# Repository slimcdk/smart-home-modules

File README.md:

# Hardware components for home automation

## Saved for furter reading
https://github.com/xesscorp/kicad-3rd-party-tools

## Setup
To fetch submodules, run the command:
```
$ git submodule update --init
```

## Contribute
You are very welcome to do pull requests. Before doing so, please read the repository guidelines.

### Repository structure

KiCad can not handle libaries outside its project folders. Therefore common libraries must be places in ```include/libs/kicad``` and any project then symlinks this directory.

E.g. this will create a symbolic link ```libs```inside the kicad project.
```
$ cd mains-light-controller/circuits
$ ln -s ./../../include/libs/kicad ./libs
```

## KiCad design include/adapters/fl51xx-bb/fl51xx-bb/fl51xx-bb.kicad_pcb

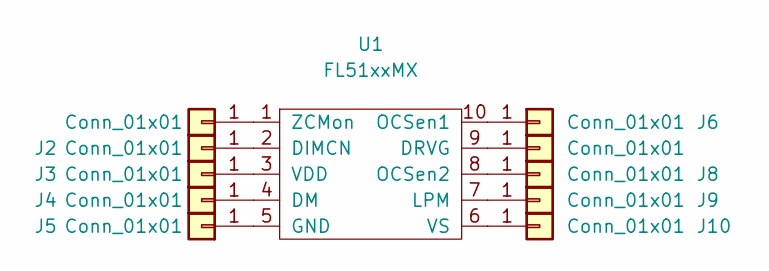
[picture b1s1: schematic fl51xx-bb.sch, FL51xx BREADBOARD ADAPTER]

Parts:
J1, J2, J3, J4, J5, J6, J7, J8, J9, J10: Conn_01x01; PinHeader_1x01_P2.54mm_Vertical
U1: FL51xxMX

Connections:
unnamed: J1.1, U1.1 (ZCMon)
unnamed: J2.1, U1.2 (DIMCN)
unnamed: J3.1, U1.3 (VDD)
unnamed: J4.1, U1.4 (DM)
unnamed: J5.1, U1.5 (GND)
unnamed: J6.1, U1.10 (OCSen1)
unnamed: J7.1, U1.9 (DRVG)
unnamed: J8.1, U1.8 (OCSen2)
unnamed: J9.1, U1.7 (LPM)
unnamed: J10.1, U1.6 (VS)

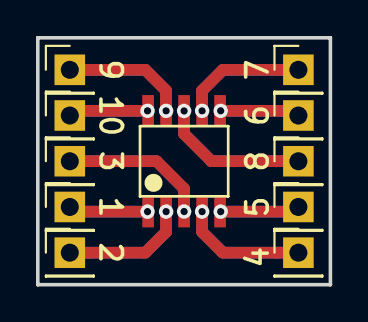
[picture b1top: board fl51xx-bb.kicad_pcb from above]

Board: 2 copper layers, 16.3 x 13.7 mm, 11 parts (0 on the bottom side), 10 nets.

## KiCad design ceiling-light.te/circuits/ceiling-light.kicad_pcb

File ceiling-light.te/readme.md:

<h1>Ceiling Light Controller</h1>

This component can control any loads of mains voltage (120-240VAC) up to 5A.
Requires constant power and sensing line (main switch) to function as intended.

<hr>
<h3>Power inputs</h3>
<ul>
    <li>M1: Power from switches</li>
    <li>M2: Constant power supply</li>
    <li>N: Neutral</li>
</ul>

<hr>
<h2>Circuit Design</h2>
<p>Schematic</p>

<p>PCB layout</p>

<div style="height: 500px; width:100%">
  
  <div style="float:left; height: 100%; width:auto;">
    <ul>
      <li><a href="exports/ceiling-light-Edge.Cuts.svg">Edge Cuts</a></li>
      <li><a href="exports/ceiling-light-F.SilkS.svg">Silkscreen Top</a></li>
      <li><a href="exports/ceiling-light-B.SilkS.svg">Silkscreen Bottom</a></li>  
      <li><a href="exports/ceiling-light-F.Mask.svg">Soldermask Top</a></li>
      <li><a href="exports/ceiling-light-B.Mask.svg">Soldermask Bottom</a></li>
      <li><a href="exports/ceiling-light-F.Cu.svg">Copper Top</a></li>
      <li><a href="exports/ceiling-light-B.Cu.svg">Copper Bottom</a></li>
    </ul>
  </div>

  <div style="margin-left:auto; margin-right:auto; height:100%; width:100%;">

  </div>
</div>

<!--hr>

<h2> BOM (Bill of Materials) </h2>
<table style="text-align:left">
  <tr><th>#</th>  <th>Quantity</th> <th>Part</th>                     <th>Section</th>        <th>Link</th>  </tr>
  <tr><td>1</td>  <td>1</td>        <td>WeMos D1 (ESP8266)</td>       <td>Controller</td>     <td></td>      </tr>
  <tr><td>2</td>  <td>1</td>        <td>WS1228b RGB LED</td>          <td></td>               <td></td>      </tr>
  <tr><td>3</td>  <td>1</td>        <td>LDR</td>                      <td></td>               <td></td>      </tr>
  <tr><td>4</td>  <td>1</td>        <td>1/4W 10k Ohms resistor</td>   <td></td>               <td></td>      </tr>
  <tr><td>5</td>  <td>1</td>        <td>01x02 Screw terminal 
                                          (5.08mm pin spacing)</td>   <td></td>               <td></td>      </tr>
  <tr><td>6</td>  <td>1</td>        <td>01x03 Screw terminal 
                                          (5.08mm pin spacing)</td>   <td></td>               <td></td>      </tr>
  <tr><td>7</td>  <td>1</td>        <td>DB107 Full bridge 
                                          rectifier</td>              <td>Sensing</td>        <td></td>      </tr>
  <tr><td>8</td>  <td>1</td>        <td>LTV-817 Optocoupler</td>      <td></td>               <td></td>      </tr>
  <tr><td>9</td>  <td>1</td>        <td>1µf Electrolytic capacitor 
                                          (min 50V)</td>              <td></td>               <td></td>      </tr>
  <tr><td>10</td> <td>1</td>        <td>1/2W 10k Ohms resistor</td>   <td></td>               <td></td>      </tr>
  <tr><td>11</td> <td>1</td>        <td>HLK-PM05 AC-DC 5V voltage 
                                          regulator</td>              <td></td>               <td></td>      </tr>
  <tr><td>12</td> <td>1</td>        <td>MOC3021 Optocoupler</td>      <td>Load switcher</td>  <td></td>      </tr>
  <tr><td>13</td> <td>1</td>        <td>BT136 Triac (500V)</td>       <td></td>               <td></td>      </tr>
  <tr><td>14</td> <td>1</td>        <td>1/2W 100 Ohms resistor</td>   <td></td>               <td></td>      </tr>
  <tr><td>15</td> <td>1</td>        <td>1/2W 10k Ohms resistor</td>   <td></td>               <td></td>      </tr>
  <tr><td>16</td> <td>1</td>        <td>1/2W 330 Ohms resistor</td>   <td></td>               <td></td>      </tr>
  <tr><td>17</td> <td>1</td>        <td>1/2W 100nf Ceramic 
                                          capacitor</td>              <td></td>               <td></td>      </tr>
</table-->

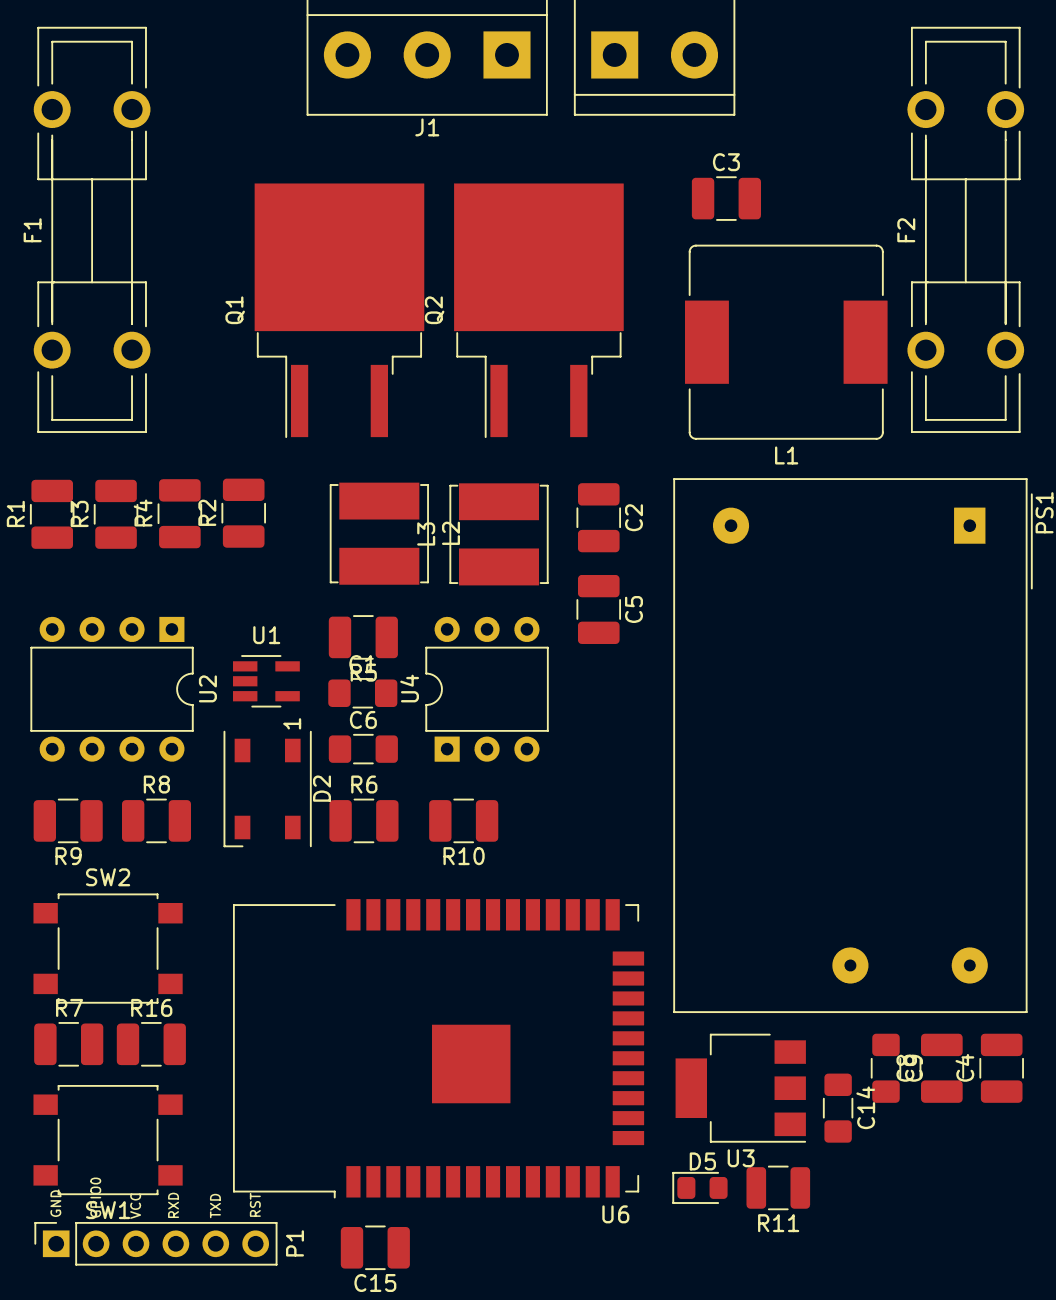
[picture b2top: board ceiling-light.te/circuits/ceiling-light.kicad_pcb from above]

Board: 2 copper layers, 42 parts (0 on the bottom side), 29 nets, no tracks yet.

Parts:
C1, C6: 0.1µ; C_1206_3216Metric_Pad1.42x1.75mm_HandSolder
C2, C3, C5, C8: 100n; C_1210_3225Metric_Pad1.42x2.65mm_HandSolder
C4: 10µF; C_1210_3225Metric_Pad1.42x2.65mm_HandSolder
C9: 47µ; C_1206_3216Metric_Pad1.42x1.75mm_HandSolder
C14: 22µF; C_1206_3216Metric_Pad1.42x1.75mm_HandSolder
C15: 10µ; C_1210_3225Metric_Pad1.42x2.65mm_HandSolder
D2: WS2812B; LED_WS2812B_PLCC4_5.0x5.0mm_P3.2mm
D5: LED; LED_0805_2012Metric_Pad1.15x1.40mm_HandSolder
F1, F2: Fuse; Fuseholder5x20_horiz_open_lateral_Type-II
J1: Screw_Terminal_01x03; TerminalBlock_bornier-3_P5.08mm
J2: Screw_Terminal_01x02; TerminalBlock_bornier-2_P5.08mm
L1: 100µH; L_Bourns_SRR1210A
L2, L3: 100µH; L_Bourns_SRN6045TA
P1: ESProg_Mating_Header; ESProg_PinSocket_1x06_P2.54mm_Vertical
PS1: IRM-02-12; Converter_ACDC_MeanWell_IRM-02-xx_THT
Q1, Q2: IRF840; TO-263-2_TabPin1
R1, R2, R3, R4: 100K; R_1210_3225Metric_Pad1.42x2.65mm_HandSolder
R5, R7, R8, R9, R16: 10K; R_1210_3225Metric_Pad1.42x2.65mm_HandSolder
R6: 1K; R_1210_3225Metric_Pad1.42x2.65mm_HandSolder
R10: 330; R_1210_3225Metric_Pad1.42x2.65mm_HandSolder
R11: 400R; R_1210_3225Metric
SW1, SW2: SW_Push; SW_SPST_B3S-1000
U1: TMP36xS; SOT-23-5_HandSoldering
U2: LTV-824; DIP-8_W7.62mm
U3: AMS1117-3.3; SOT-223
U4: 4N35; DIP-6_W7.62mm
U6: ESP32-WROOM-32D; ESP32-WROOM-32

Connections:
+3V3: C6.1, C14.1, C15.1, D2.1, P1.3, R7.1, R8.1, R9.1, R11.1, R16.1, U3.2, U6.2
+12V: C4.2, C8.2, C9.1, PS1.4, U3.3, U4.5
/ESP32_BOOT: P1.2, R7.2, SW2.2, U6.25
/ESP32_RST: P1.6, R16.2, SW1.2, U6.3
/ESP32_RXD: P1.4, U6.34
/ESP32_TXD: P1.5, U6.35
GND: C1.2, C4.1, C6.2, C8.1, C9.2, C14.2, C15.2, D2.3, D5.1, P1.1, PS1.3, R5.2, R6.2, SW1.1, SW2.1, U1.4, U2.5, U2.7, U3.1, U4.2, U6.1, U6.15, U6.38
unnamed: C1.1, U1.5
unnamed: C2.1, F1.1, L2.1, Q1.2, R1.2, R3.2
unnamed: C2.2, C3.1, J1.1, J2.1, L3.2
unnamed: C3.2, F2.1, L1.1
unnamed: C5.1, L3.1, PS1.1
unnamed: C5.2, L2.2, PS1.2
unnamed: D2.4, R6.1, U6.7
unnamed: D5.2, R11.2
unnamed: F1.2, J1.3
unnamed: F2.2, J2.2
unnamed: J1.2, R2.2, R4.2
unnamed: L1.2, Q2.2
unnamed: Q1.1, Q2.1, R5.1, U4.4
unnamed: R1.1, U2.3
unnamed: R2.1, U2.4
unnamed: R3.1, U2.1
unnamed: R4.1, U2.2
unnamed: R8.2, U2.8, U6.14
unnamed: R9.2, U2.6, U6.13
unnamed: R10.1, U6.37
unnamed: R10.2, U4.1
unnamed: U1.1, U6.4

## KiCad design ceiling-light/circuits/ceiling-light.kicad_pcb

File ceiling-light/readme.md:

<h1>Ceiling Light Controller</h1>

This component can control any loads of mains voltage (120-240VAC) up to 5A.
Requires constant power and sensing line (main switch) to function as intended.

<hr>
<h3>Power inputs</h3>
<ul>
    <li>M1: Power from switches</li>
    <li>M2: Constant power supply</li>
    <li>N: Neutral</li>
</ul>

<hr>
<h2>Circuit Design</h2>
<p>Schematic</p>

<p>PCB layout</p>

<div style="height: 500px; width:100%">
  
  <div style="float:left; height: 100%; width:auto;">
    <ul>
      <li><a href="exports/ceiling-light-Edge.Cuts.svg">Edge Cuts</a></li>
      <li><a href="exports/ceiling-light-F.SilkS.svg">Silkscreen Top</a></li>
      <li><a href="exports/ceiling-light-B.SilkS.svg">Silkscreen Bottom</a></li>  
      <li><a href="exports/ceiling-light-F.Mask.svg">Soldermask Top</a></li>
      <li><a href="exports/ceiling-light-B.Mask.svg">Soldermask Bottom</a></li>
      <li><a href="exports/ceiling-light-F.Cu.svg">Copper Top</a></li>
      <li><a href="exports/ceiling-light-B.Cu.svg">Copper Bottom</a></li>
    </ul>
  </div>

  <div style="margin-left:auto; margin-right:auto; height:100%; width:100%;">

  </div>
</div>

<hr>

<h2> BOM (Bill of Materials) </h2>
<table style="text-align:left">
  <tr><th>#</th>  <th>Quantity</th> <th>Part</th>                     <th>Section</th>        <th>Link</th>  </tr>
  <tr><td>1</td>  <td>1</td>        <td>WeMos D1 (ESP8266)</td>       <td>Controller</td>     <td></td>      </tr>
  <tr><td>2</td>  <td>1</td>        <td>WS1228b RGB LED</td>          <td></td>               <td></td>      </tr>
  <tr><td>3</td>  <td>1</td>        <td>LDR</td>                      <td></td>               <td></td>      </tr>
  <tr><td>4</td>  <td>1</td>        <td>1/4W 10k Ohms resistor</td>   <td></td>               <td></td>      </tr>
  <tr><td>5</td>  <td>1</td>        <td>01x02 Screw terminal 
                                          (5.08mm pin spacing)</td>   <td></td>               <td></td>      </tr>
  <tr><td>6</td>  <td>1</td>        <td>01x03 Screw terminal 
                                          (5.08mm pin spacing)</td>   <td></td>               <td></td>      </tr>
  <tr><td>7</td>  <td>1</td>        <td>DB107 Full bridge 
                                          rectifier</td>              <td>Sensing</td>        <td></td>      </tr>
  <tr><td>8</td>  <td>1</td>        <td>LTV-817 Optocoupler</td>      <td></td>               <td></td>      </tr>
  <tr><td>9</td>  <td>1</td>        <td>1µf Electrolytic capacitor 
                                          (min 50V)</td>              <td></td>               <td></td>      </tr>
  <tr><td>10</td> <td>1</td>        <td>1/2W 10k Ohms resistor</td>   <td></td>               <td></td>      </tr>
  <tr><td>11</td> <td>1</td>        <td>HLK-PM05 AC-DC 5V voltage 
                                          regulator</td>              <td></td>               <td></td>      </tr>
  <tr><td>12</td> <td>1</td>        <td>MOC3021 Optocoupler</td>      <td>Load switcher</td>  <td></td>      </tr>
  <tr><td>13</td> <td>1</td>        <td>BT136 Triac (500V)</td>       <td></td>               <td></td>      </tr>
  <tr><td>14</td> <td>1</td>        <td>1/2W 100 Ohms resistor</td>   <td></td>               <td></td>      </tr>
  <tr><td>15</td> <td>1</td>        <td>1/2W 10k Ohms resistor</td>   <td></td>               <td></td>      </tr>
  <tr><td>16</td> <td>1</td>        <td>1/2W 330 Ohms resistor</td>   <td></td>               <td></td>      </tr>
  <tr><td>17</td> <td>1</td>        <td>1/2W 100nf Ceramic 
                                          capacitor</td>              <td></td>               <td></td>      </tr>
</table>

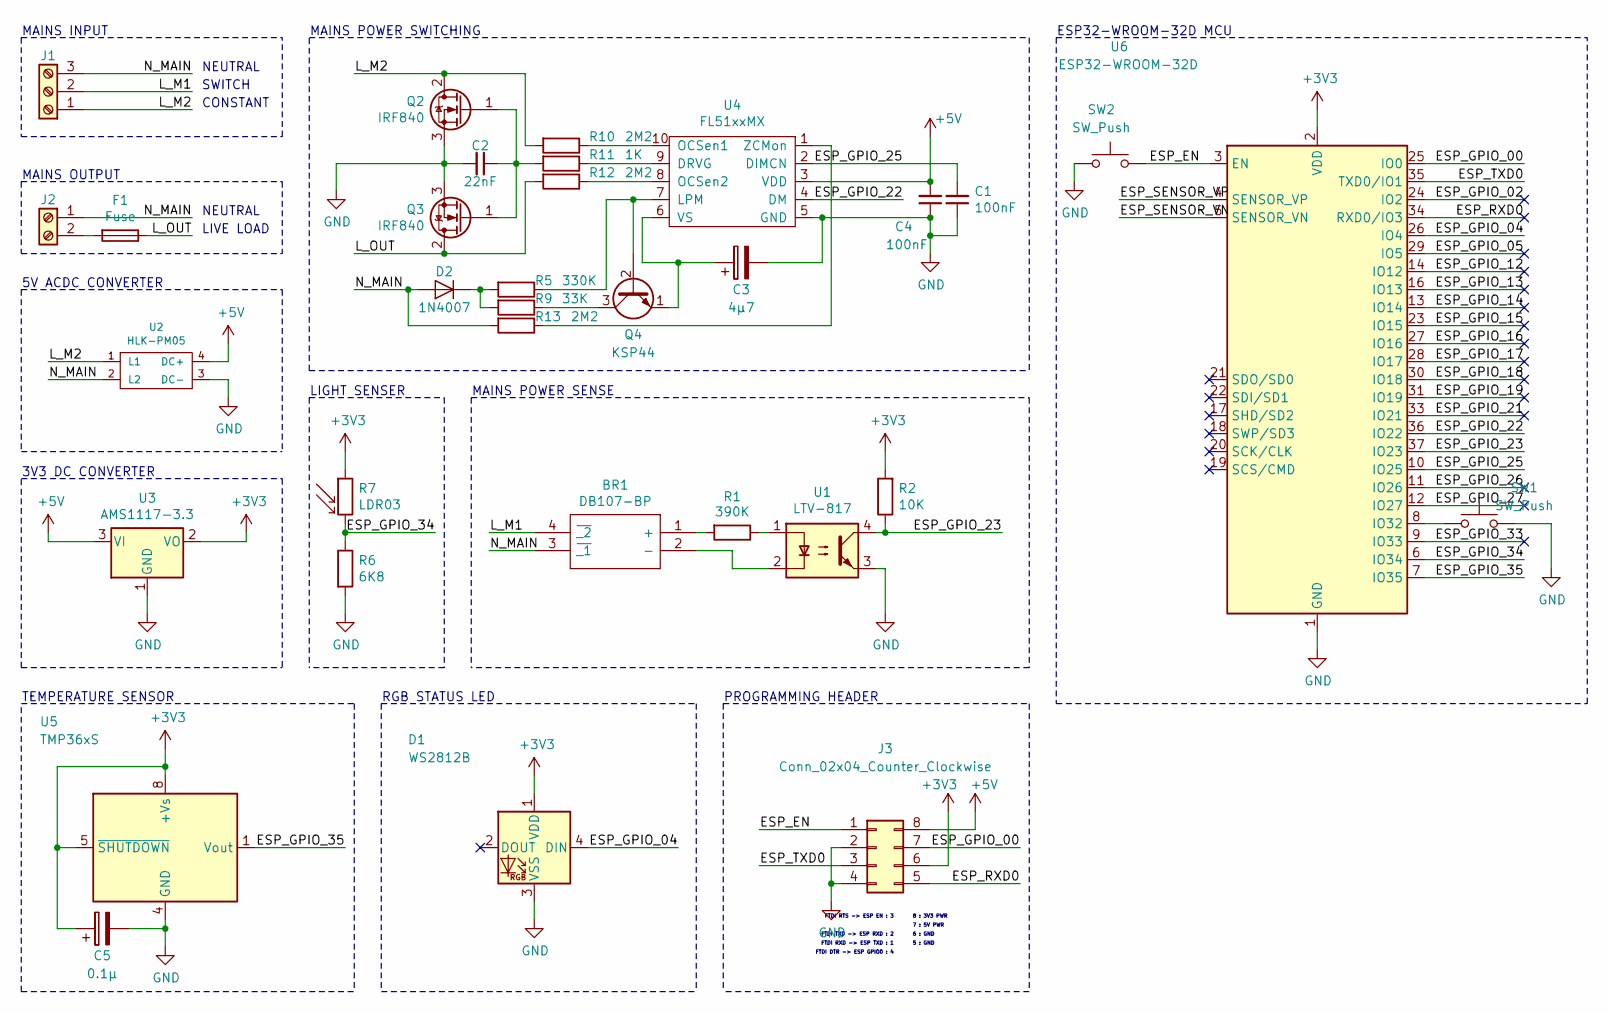
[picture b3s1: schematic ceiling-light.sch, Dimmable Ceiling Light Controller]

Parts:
BR1: DB107-BP; Manufacturer_Part_Number DB107-BP; Mouser Part Number 833-DB107-BP
C1, C4: 100nF; CP_Radial_D5.0mm_P2.50mm
C2: 22nF; CP_Radial_D5.0mm_P2.50mm
C3: 4µ7; CP_Radial_D5.0mm_P2.50mm
C5: 0.1µ; CP_Radial_D5.0mm_P2.50mm
D1: WS2812B; LED_WS2812B_PLCC4_5.0x5.0mm_P3.2mm
D2: 1N4007; D_DO-41_SOD81_P10.16mm_Horizontal
F1: Fuse; Fuseholder5x20_horiz_open_lateral_Type-II
J1: Screw_Terminal_01x03; TerminalBlock_bornier-3_P5.08mm
J2: Screw_Terminal_01x02; TerminalBlock_bornier-2_P5.08mm
J3: Conn_02x04_Counter_Clockwise; PinSocket_2x04_P2.54mm_Vertical
Q2, Q3: IRF840; TO-263-3_TabPin2
Q4: KSP44; TO-92_Inline
R1: 390K; R_Axial_DIN0207_L6.3mm_D2.5mm_P10.16mm_Horizontal
R2: 10K; R_Axial_DIN0207_L6.3mm_D2.5mm_P10.16mm_Horizontal
R5: 330K; R_Axial_DIN0207_L6.3mm_D2.5mm_P10.16mm_Horizontal
R6: 6K8; R_Axial_DIN0207_L6.3mm_D2.5mm_P10.16mm_Horizontal
R7: LDR03; R_LDR_5.0x4.1mm_P3mm_Vertical
R9: 33K; R_Axial_DIN0207_L6.3mm_D2.5mm_P10.16mm_Horizontal
R10, R12, R13: 2M2; R_Axial_DIN0411_L9.9mm_D3.6mm_P12.70mm_Horizontal
R11: 1K; R_Axial_DIN0207_L6.3mm_D2.5mm_P10.16mm_Horizontal
SW1, SW2: SW_Push; SW_Tactile_Straight_KSA0Axx1LFTR
U1: LTV-817; DIP-4_W7.62mm
U2: HLK-PM05; HLK-PM01
U3: AMS1117-3.3; SOT-223-3_TabPin2
U4: FL51xxMX
U5: TMP36xS; SOIC-8_3.9x4.9mm_P1.27mm
U6: ESP32-WROOM-32D; ESP32-WROOM-32

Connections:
+3V3: C5.1, D1.1 (VDD), J3.6, R2.2, R7.1, U3.2 (VO), U5.5 (~SHUTDOWN), U5.8 (+Vs), U6.2 (VDD)
+5V: C4.2, J3.8, U2.4 (DC+), U3.3 (VI), U4.3 (VDD)
/ESP_EN: J3.1, SW2.2, U6.3 (EN)
/ESP_GPIO_00: J3.7, U6.25 (IO0)
/ESP_GPIO_02: U6.24 (IO2)
/ESP_GPIO_04: D1.4 (DIN), U6.26 (IO4)
/ESP_GPIO_05: U6.29 (IO5)
/ESP_GPIO_12: U6.14 (IO12)
/ESP_GPIO_13: U6.16 (IO13)
/ESP_GPIO_14: U6.13 (IO14)
/ESP_GPIO_15: U6.23 (IO15)
/ESP_GPIO_16: U6.27 (IO16)
/ESP_GPIO_17: U6.28 (IO17)
/ESP_GPIO_18: U6.30 (IO18)
/ESP_GPIO_19: U6.31 (IO19)
/ESP_GPIO_21: U6.33 (IO21)
/ESP_GPIO_22: U4.4 (DM), U6.36 (IO22)
/ESP_GPIO_23: R2.1, U1.4, U6.37 (IO23)
/ESP_GPIO_25: C1.2, U4.2 (DIMCN), U6.10 (IO25)
/ESP_GPIO_26: U6.11 (IO26)
/ESP_GPIO_27: U6.12 (IO27)
/ESP_GPIO_33: U6.9 (IO33)
/ESP_GPIO_34: R6.1, R7.2, U6.6 (IO34)
/ESP_GPIO_35: U5.1 (Vout), U6.7 (IO35)
/ESP_RXD0: J3.5, U6.34 (RXD0/IO3)
/ESP_SENSOR_VN: U6.5 (SENSOR_VN)
/ESP_SENSOR_VP: U6.4 (SENSOR_VP)
/ESP_TXD0: J3.3, U6.35 (TXD0/IO1)
/L_M1: BR1.4 (~_2), J1.2
/L_M2: J1.1, Q2.2 (D), R10.2, U2.1 (L1)
/L_OUT: F1.1, Q3.2 (D), R12.2
/N_MAIN: BR1.3 (~_1), D2.2 (A), J1.3, J2.1, R13.2, U2.2 (L2)
GND: C1.1, C2.2, C3.2, C4.1, C5.2, D1.3 (VSS), J3.2, J3.4, Q2.3 (S), Q3.3 (S), R6.2, SW1.2, SW2.1, U1.3, U2.3 (DC-), U3.1 (GND), U4.5 (GND), U5.4 (GND), U6.1 (GND), U6.15 (GND), U6.38 (GND)
unnamed: BR1.1 (+), R1.2
unnamed: BR1.2 (-), U1.2
unnamed: C2.1, Q2.1 (G), Q3.1 (G), R11.2
unnamed: C3.1, Q4.1 (E), U4.6 (VS)
unnamed: D2.1 (K), R5.2, R9.2
unnamed: F1.2, J2.2
unnamed: Q4.2 (B), R5.1, U4.7 (LPM)
unnamed: Q4.3 (C), R9.1
unnamed: R1.1, U1.1
unnamed: R10.1, U4.10 (OCSen1)
unnamed: R11.1, U4.9 (DRVG)
unnamed: R12.1, U4.8 (OCSen2)
unnamed: R13.1, U4.1 (ZCMon)
unnamed: SW1.1, U6.8 (IO32)

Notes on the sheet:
NEUTRAL
SWITCH
CONSTANT
LIVE LOAD
MAINS INPUT
5V ACDC CONVERTER
MAINS POWER SENSE
MAINS POWER SWITCHING
MAINS OUTPUT
LIGHT SENSER
RGB STATUS LED
3V3 DC CONVERTER
TEMPERATURE SENSOR
ESP32-WROOM-32D MCU
8 : 3V3 PWR
FTDI RTS -> ESP EN : 3
FTDI TXD -> ESP RXD : 2
FTDI RXD -> ESP TXD : 1
5 : GND
7 : 5V PWR
PROGRAMMING HEADER
6 : GND
FTDI DTR -> ESP GPIO0 : 4

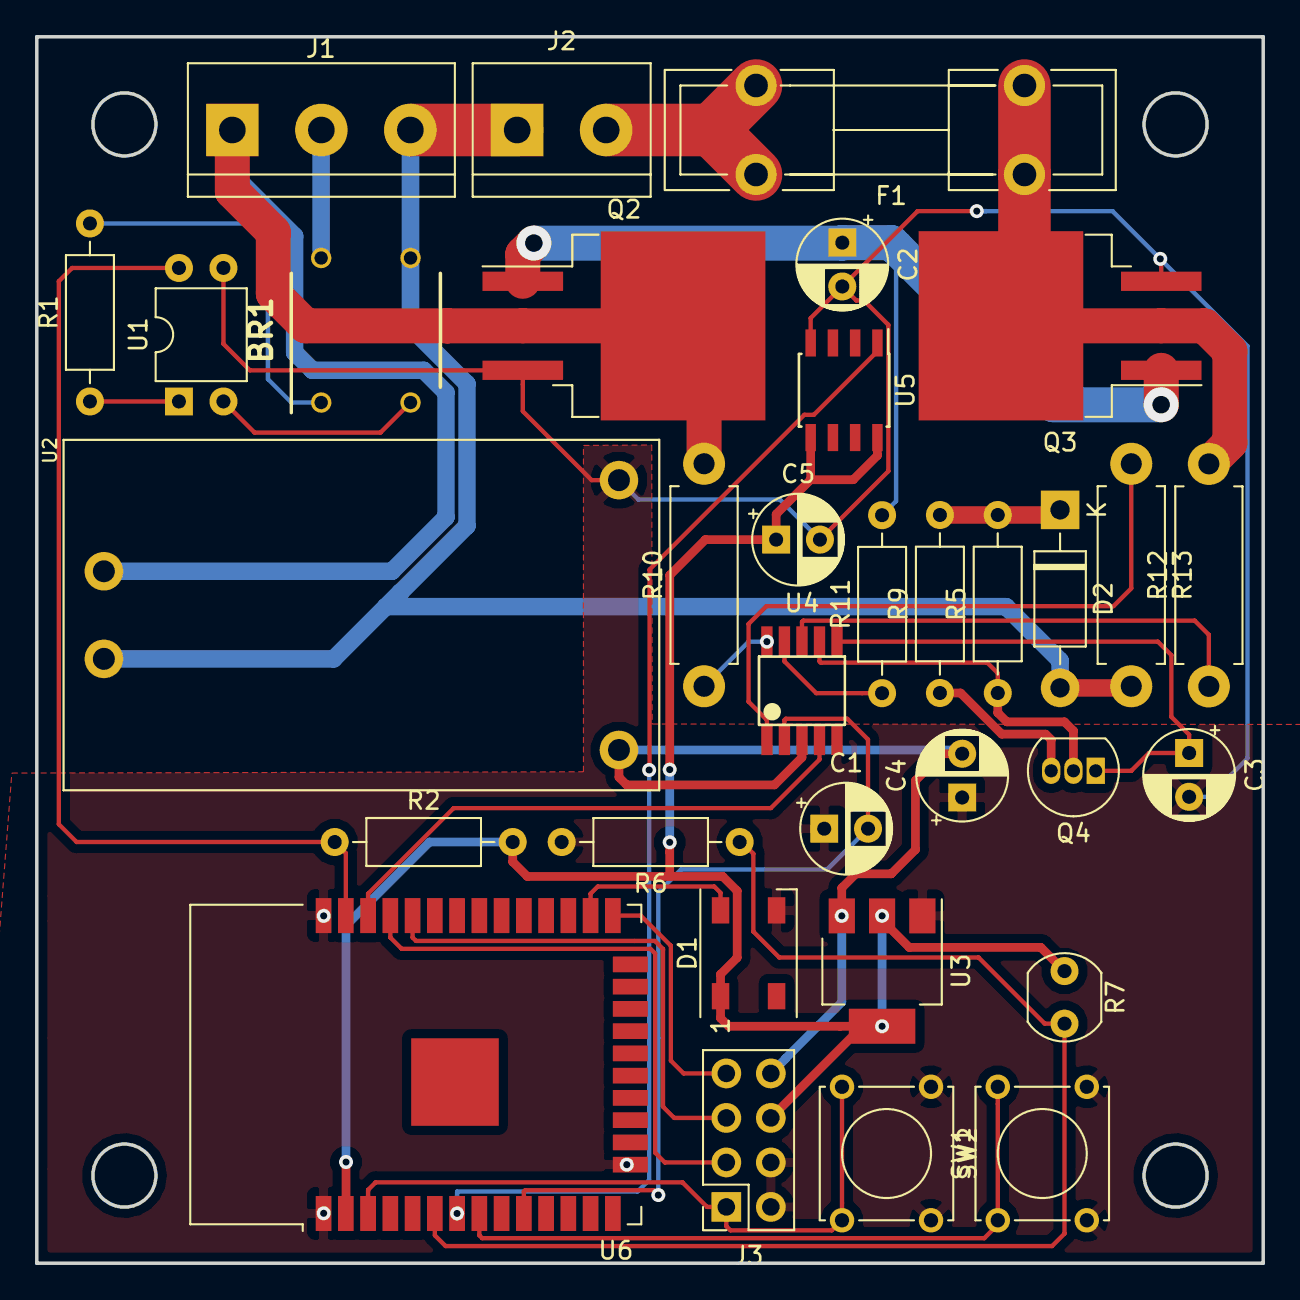
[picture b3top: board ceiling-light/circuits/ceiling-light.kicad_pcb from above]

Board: 2 copper layers, 70.0 x 70.0 mm, 33 parts (0 on the bottom side), 31 nets.

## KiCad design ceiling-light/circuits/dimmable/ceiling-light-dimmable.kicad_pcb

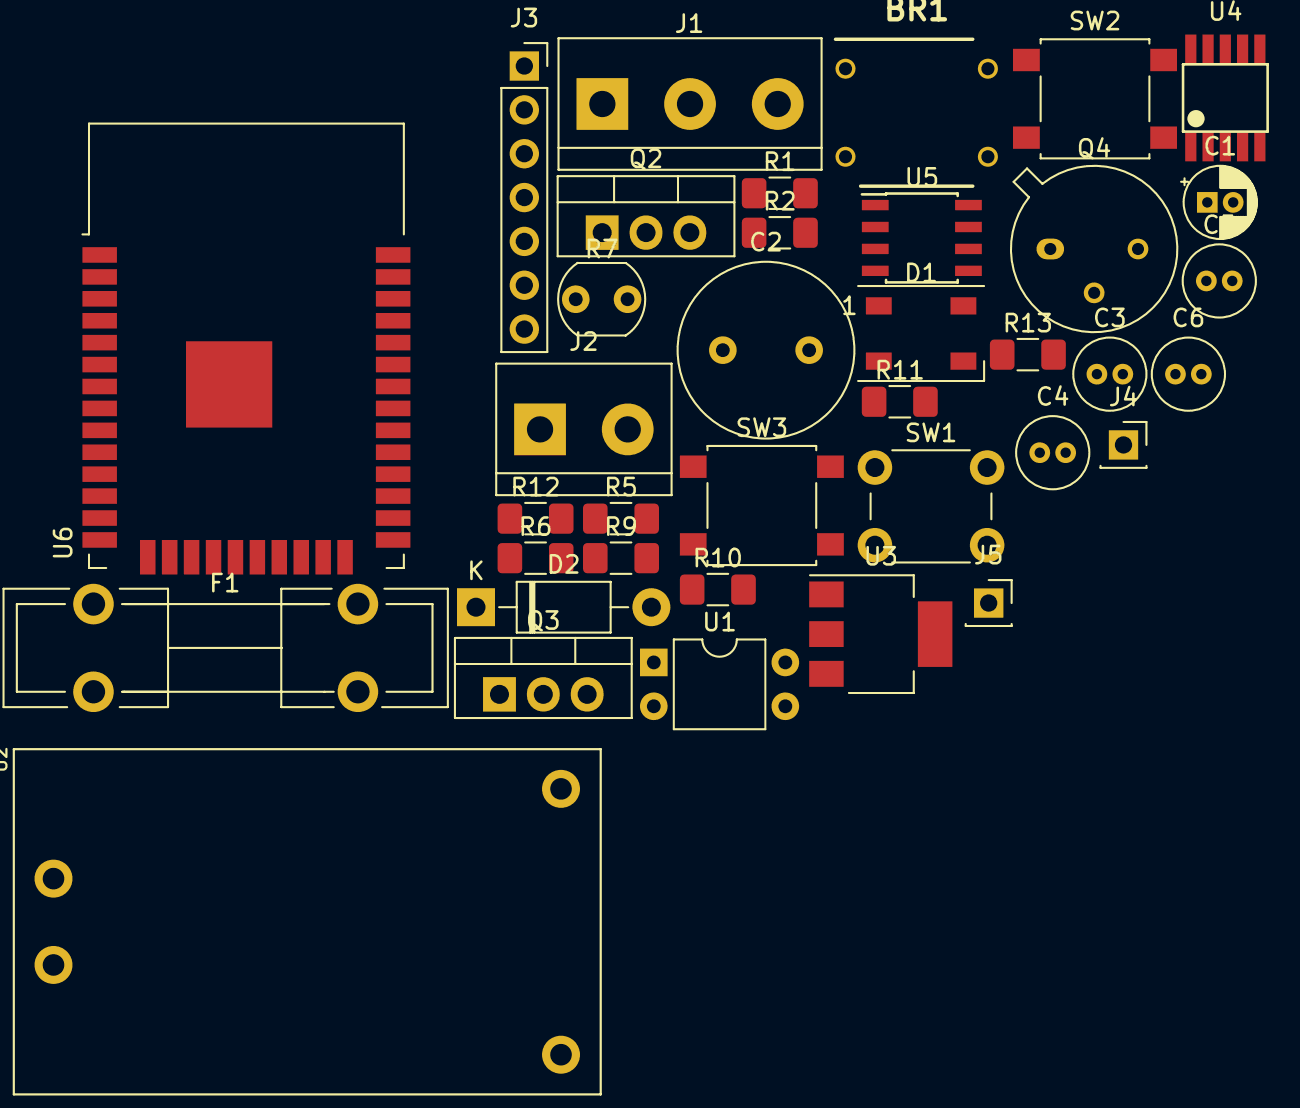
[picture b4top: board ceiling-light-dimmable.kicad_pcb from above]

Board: 2 copper layers, 37 parts (0 on the bottom side), 31 nets, no tracks yet.

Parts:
BR1: DB107-BP
C1: 1µF; CP_Radial_D4.0mm_P1.50mm
C2: 22nF; C_Radial_D10.0mm_H12.5mm_P5.00mm
C3: 22nF; C_Radial_D4.0mm_H5.0mm_P1.50mm
C4: 100nF; C_Radial_D4.0mm_H5.0mm_P1.50mm
C5, C6: 0.1µF; C_Radial_D4.0mm_H5.0mm_P1.50mm
D1: WS2812B; LED_WS2812B_PLCC4_5.0x5.0mm_P3.2mm
D2: 1N4007; D_DO-41_SOD81_P10.16mm_Horizontal
F1: Fuse; Fuseholder5x20_horiz_open_lateral_Type-II
J1: Screw_Terminal_01x03; TerminalBlock_bornier-3_P5.08mm
J2: Screw_Terminal_01x02; TerminalBlock_bornier-2_P5.08mm
J3: Conn_01x07; PinSocket_1x07_P2.54mm_Vertical
J4, J5: Conn_01x01; PinSocket_1x01_P2.54mm_Vertical
Q2, Q3: IRF840; TO-220-3_Vertical
Q4: KSP44; TO-39-3
R1: 390K; R_1206_3216Metric_Pad1.42x1.75mm_HandSolder
R2: 10K; R_1206_3216Metric_Pad1.42x1.75mm_HandSolder
R5: 330K; R_1206_3216Metric_Pad1.42x1.75mm_HandSolder
R6: 6K8; R_1206_3216Metric_Pad1.42x1.75mm_HandSolder
R7: LDR03; R_LDR_5.0x4.1mm_P3mm_Vertical
R9: 33K; R_1206_3216Metric_Pad1.42x1.75mm_HandSolder
R10, R12, R13: 2M; R_1206_3216Metric_Pad1.42x1.75mm_HandSolder
R11: 1K; R_1206_3216Metric_Pad1.42x1.75mm_HandSolder
SW1: SW_Push; SW_PUSH_6mm
SW2, SW3: SW_Push; SW_SPST_B3S-1000
U1: LTV-817; DIP-4_W7.62mm
U2: HLK-PM05; HLK-PM01
U3: AMS1117-3.3; SOT-223-3_TabPin2
U4: FL51xxMX
U5: TMP36xS; SOIC-8_3.9x4.9mm_P1.27mm
U6: ESP32-WROOM-32D; ESP32-WROOM-32

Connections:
+3V3: C5.1, C6.1, D1.1, J3.6, R2.2, R7.1, U3.2, U5.5, U5.8, U6.2
+5V: C4.2, J3.1, U2.4, U3.3, U4.8
/DIMCN: J4.1, U4.9
/DIM_MODE: J5.1, U4.7
/ESP_FLASH: J3.5, SW3.1, U6.25
/ESP_RX: J3.4, U6.34
/ESP_TX: J3.3, U6.35
/LIGHT_SENSE: R6.1, R7.2, U6.5
/L_OUT: F1.1, Q3.2, R12.2
/M1_IN: BR1.4, J1.2
/M2_IN: J1.1, Q2.2, R10.2, U2.1
/MAINS_SENSE: C1.1, R2.1, U1.4, U6.6
/N_MAIN: BR1.3, D2.2, J1.3, J2.1, R13.1, U2.2
/STATUS_LED: D1.4, U6.9
/TEMP_SENSE: U5.1, U6.4
GND: C1.2, C2.2, C3.2, C4.1, C5.2, C6.2, D1.3, J3.2, J3.7, Q2.3, Q3.3, R6.2, SW1.2, SW2.1, SW3.2, U1.3, U2.3, U3.1, U4.6, U5.4, U6.1, U6.15, U6.38
unnamed: BR1.1, R1.2
unnamed: BR1.2, U1.2
unnamed: C2.1, Q2.1, Q3.1, R11.2
unnamed: C3.1, Q4.1, U4.5
unnamed: D2.1, R5.2, R9.2
unnamed: F1.2, J2.2
unnamed: Q4.2, R5.1, U4.4
unnamed: Q4.3, R9.1
unnamed: R1.1, U1.1
unnamed: R10.1, U4.1
unnamed: R11.1, U4.2
unnamed: R12.1, U4.3
unnamed: R13.2, U4.10
unnamed: SW1.1, U6.8
unnamed: SW2.2, U6.3

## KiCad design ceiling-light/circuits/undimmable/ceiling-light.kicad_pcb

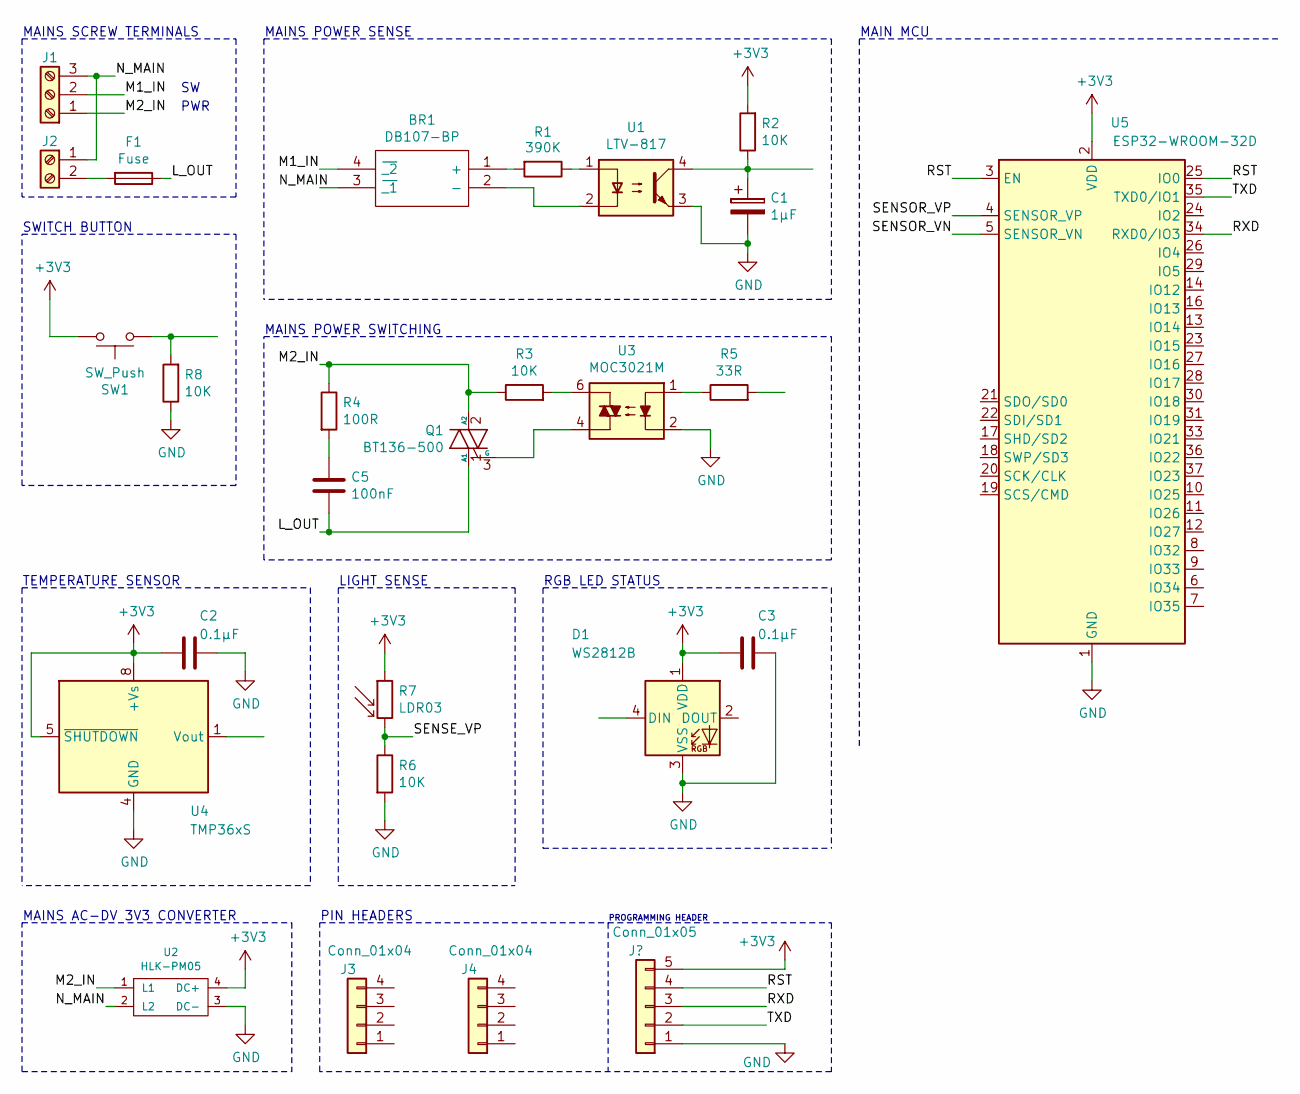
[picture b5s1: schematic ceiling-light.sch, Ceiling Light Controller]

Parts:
BR1: DB107-BP; DIP825W56P510L828H330Q4N; Manufacturer_Part_Number DB107-BP; Mouser Part Number 833-DB107-BP
C1: 1µF; CP_Radial_D4.0mm_P1.50mm
C2, C3: 0.1µF; C_Disc_D5.1mm_W3.2mm_P5.00mm
C5: 100nF; C_Disc_D5.1mm_W3.2mm_P5.00mm
D1: WS2812B; LED_WS2812B_PLCC4_5.0x5.0mm_P3.2mm
F1: Fuse; Fuseholder5x20_horiz_open_lateral_Type-II
J1: Screw_Terminal_01x03; TerminalBlock_bornier-3_P5.08mm
J2: Screw_Terminal_01x02; TerminalBlock_bornier-2_P5.08mm
J3, J4: Conn_01x04; PinHeader_1x04_P2.54mm_Vertical
Q1: BT136-500; TO-220-3_Horizontal_TabUp
R1: 390K; R_1206_3216Metric_Pad1.42x1.75mm_HandSolder
R2, R3, R6, R8: 10K; R_1206_3216Metric_Pad1.42x1.75mm_HandSolder
R4: 100R; R_2010_5025Metric_Pad1.52x2.65mm_HandSolder
R5: 33R; R_1206_3216Metric_Pad1.42x1.75mm_HandSolder
R7: LDR03; R_LDR_5.0x4.1mm_P3mm_Vertical
SW1: SW_Push; SW_PUSH_6mm
U1: LTV-817; DIP-4_W7.62mm
U2: HLK-PM05; HLK-PM01
U3: MOC3021M; DIP-6_W7.62mm
U4: TMP36xS; SOIC-8_3.9x4.9mm_P1.27mm
U5: ESP32-WROOM-32D; ESP32-WROOM-32

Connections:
+3V3: C2.2, C3.2, D1.1 (VDD), R2.2, R7.1, SW1.2, U2.4 (DC+), U4.5 (~SHUTDOWN), U4.8 (+Vs), U5.2 (VDD)
/RXD: U5.34 (RXD0/IO3); also elsewhere on the board
/TXD: U5.35 (TXD0/IO1); also elsewhere on the board
GND: C1.2, C2.1, C3.1, D1.3 (VSS), R6.2, R8.1, U1.3, U2.3 (DC-), U3.2, U4.4 (GND), U5.1 (GND), U5.15 (GND), U5.38 (GND); also elsewhere on the board
L_OUT: C5.2, F1.1, Q1.1 (A1)
M1_IN: BR1.4 (~_2), J1.2
M2_IN: J1.1, Q1.2 (A2), R3.1, R4.1, U2.1 (L1)
N_MAIN: BR1.3 (~_1), J1.3, J2.1, U2.2 (L2)
unnamed: BR1.1 (+), R1.2
unnamed: BR1.2 (-), U1.2
unnamed: C1.1, R2.1, U1.4
unnamed: C5.1, R4.2
unnamed: F1.2, J2.2
unnamed: Q1.3 (G), U3.4
unnamed: R1.1, U1.1
unnamed: R3.2, U3.6
unnamed: R5.1, U3.1
unnamed: R6.1, R7.2
unnamed: R8.2, SW1.1

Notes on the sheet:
PWR
MAINS SCREW TERMINALS
MAINS AC-DV 3V3 CONVERTER
MAINS POWER SENSE
MAINS POWER SWITCHING
LIGHT SENSE
RGB LED STATUS
SWITCH BUTTON
TEMPERATURE SENSOR
MAIN MCU
PIN HEADERS
PROGRAMMING HEADER

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
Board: 2 copper layers, 27 parts (0 on the bottom side), 19 nets, no tracks yet.

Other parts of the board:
J5: Conn_01x04; PinHeader_1x04_P2.54mm_Vertical

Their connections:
/RXD: J5.3; also elsewhere on the board
/TXD: J5.4; also elsewhere on the board
GND: J5.1; also elsewhere on the board

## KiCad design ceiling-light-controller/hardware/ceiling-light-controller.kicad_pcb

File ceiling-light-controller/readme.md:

# Ceiling Light Controller

This component fits the general ceiling light socket in Denmark.

<hr>
<h3>Inputs</h3>
<ul>
    <li>M1: Power from switches</li>
    <li>M2: Constant power supply</li>
    <li>N: Neutral</li>
</ul>

<br>
<hr>

<h3> Parts list </h3>
<table style="text-align:left">
  <tr> <th>#</th> <th>Quantity</th>  <th>Part</th> <th>Section</th> <th>Link</th> </tr>
  <tr> <td>1</td> <td>1</td> <td>WeMos D1 (ESP8266)</td> <td>Controller</td> <td></td> </tr>
  <tr> <td>2</td> <td>1</td> <td>WS1228b RGB LED</td> <td></td> <td></td> </tr>
  <tr> <td>3</td> <td>1</td> <td>LDR</td> <td></td> <td></td> </tr>
  <tr> <td>4</td> <td>1</td> <td>1/4W 10k Ohms resistor</td> <td></td> <td></td> </tr>
  <tr> <td>5</td> <td>1</td> <td>01x02 Screw terminal (5.08mm pin spacing)</td> <td></td> <td></td> </tr>
  <tr> <td>6</td> <td>1</td> <td>01x03 Screw terminal (5.08mm pin spacing)</td> <td></td> <td></td> </tr>
  <tr> <td>7</td> <td>1</td> <td>DB107 Full bridge rectifier</td> <td>Sensing</td> <td></td> </tr>
  <tr> <td>8</td> <td>1</td> <td>LTV-817 Optocoupler</td> <td></td> <td></td> </tr>
  <tr> <td>9</td> <td>1</td> <td>1µf Electrolytic capacitor (min 50V)</td> <td></td> <td></td> </tr>
  <tr> <td>10</td> <td>1</td> <td>1/2W 10k Ohms resistor</td> <td></td> <td></td> </tr>
  <tr> <td>11</td> <td>1</td> <td>HLK-PM05 AC-DC 5V voltage regulator</td> <td></td> <td></td> </tr>
  <tr> <td>12</td> <td>1</td> <td>MOC3021 Optocoupler</td> <td>Load controller</td> <td></td> </tr>
  <tr> <td>13</td> <td>1</td> <td>BT136 Triac (500V)</td> <td></td> <td></td> </tr>
  <tr> <td>14</td> <td>1</td> <td>1/2W 100 Ohms resistor</td> <td></td> <td></td> </tr>
  <tr> <td>15</td> <td>1</td> <td>1/2W 10k Ohms resistor</td> <td></td> <td></td> </tr>
  <tr> <td>16</td> <td>1</td> <td>1/2W 330 Ohms resistor</td> <td></td> <td></td> </tr>
  <tr> <td>17</td> <td>1</td> <td>1/2W 100nf Ceramic capacitor</td> <td></td> <td></td> </tr>
</table>

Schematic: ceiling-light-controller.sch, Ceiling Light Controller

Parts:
BR1: DB107-BP; DIP825W56P510L828H330Q4N; Manufacturer_Part_Number DB107-BP; Mouser Part Number 833-DB107-BP
C1: 1µf; CP_Radial_D4.0mm_P1.50mm
C5: 100nf; C_Disc_D5.1mm_W3.2mm_P5.00mm
D1: WS2812B; LED_WS2812B_PLCC4_5.0x5.0mm_P3.2mm
J1: Screw_Terminal_01x03; TerminalBlock_bornier-3_P5.08mm
J2: Screw_Terminal_01x02; TerminalBlock_bornier-2_P5.08mm
Q1: BT136-500; TO-220-3_Vertical_Triode_Heatsink
R1: 390k; R_Axial_DIN0309_L9.0mm_D3.2mm_P12.70mm_Horizontal
R2, R3: 10k; R_Axial_DIN0309_L9.0mm_D3.2mm_P12.70mm_Horizontal
R4: 100; R_Axial_DIN0309_L9.0mm_D3.2mm_P12.70mm_Horizontal
R5: 330; R_Axial_DIN0309_L9.0mm_D3.2mm_P12.70mm_Horizontal
R6: 10000; R_Axial_DIN0309_L9.0mm_D3.2mm_P12.70mm_Horizontal
R7: LDR03; R_LDR_10x8.5mm_P7.6mm_Vertical
U1: LTV-817; DIP-4_W7.62mm
U2: HLK-PM03; HLK-PM01
U3: MOC3021M; DIP-6_W7.62mm
U4: WeMos_mini; wemos-d1-mini-embedded

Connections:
GND: C1.2, D1.3, R6.2, U1.3, U2.3, U3.2, U4.2
unnamed: BR1.1, R1.2
unnamed: BR1.2, U1.2
unnamed: BR1.3, J1.2
unnamed: BR1.4, J1.3, J2.1, U2.1
unnamed: C1.1, R2.2, U1.4, U4.3
unnamed: C5.1, R4.2
unnamed: C5.2, J2.2, Q1.1 (A1)
unnamed: D1.1, R2.1, U2.4, U4.1
unnamed: D1.4, U4.5
unnamed: J1.1, Q1.2 (A2), R3.1, R4.1, U2.2
unnamed: Q1.3 (G), U3.4
unnamed: R1.1, U1.1
unnamed: R3.2, U3.6
unnamed: R5.1, U3.1
unnamed: R5.2, U4.4
unnamed: R6.1, R7.2, U4.10
unnamed: R7.1, U4.16

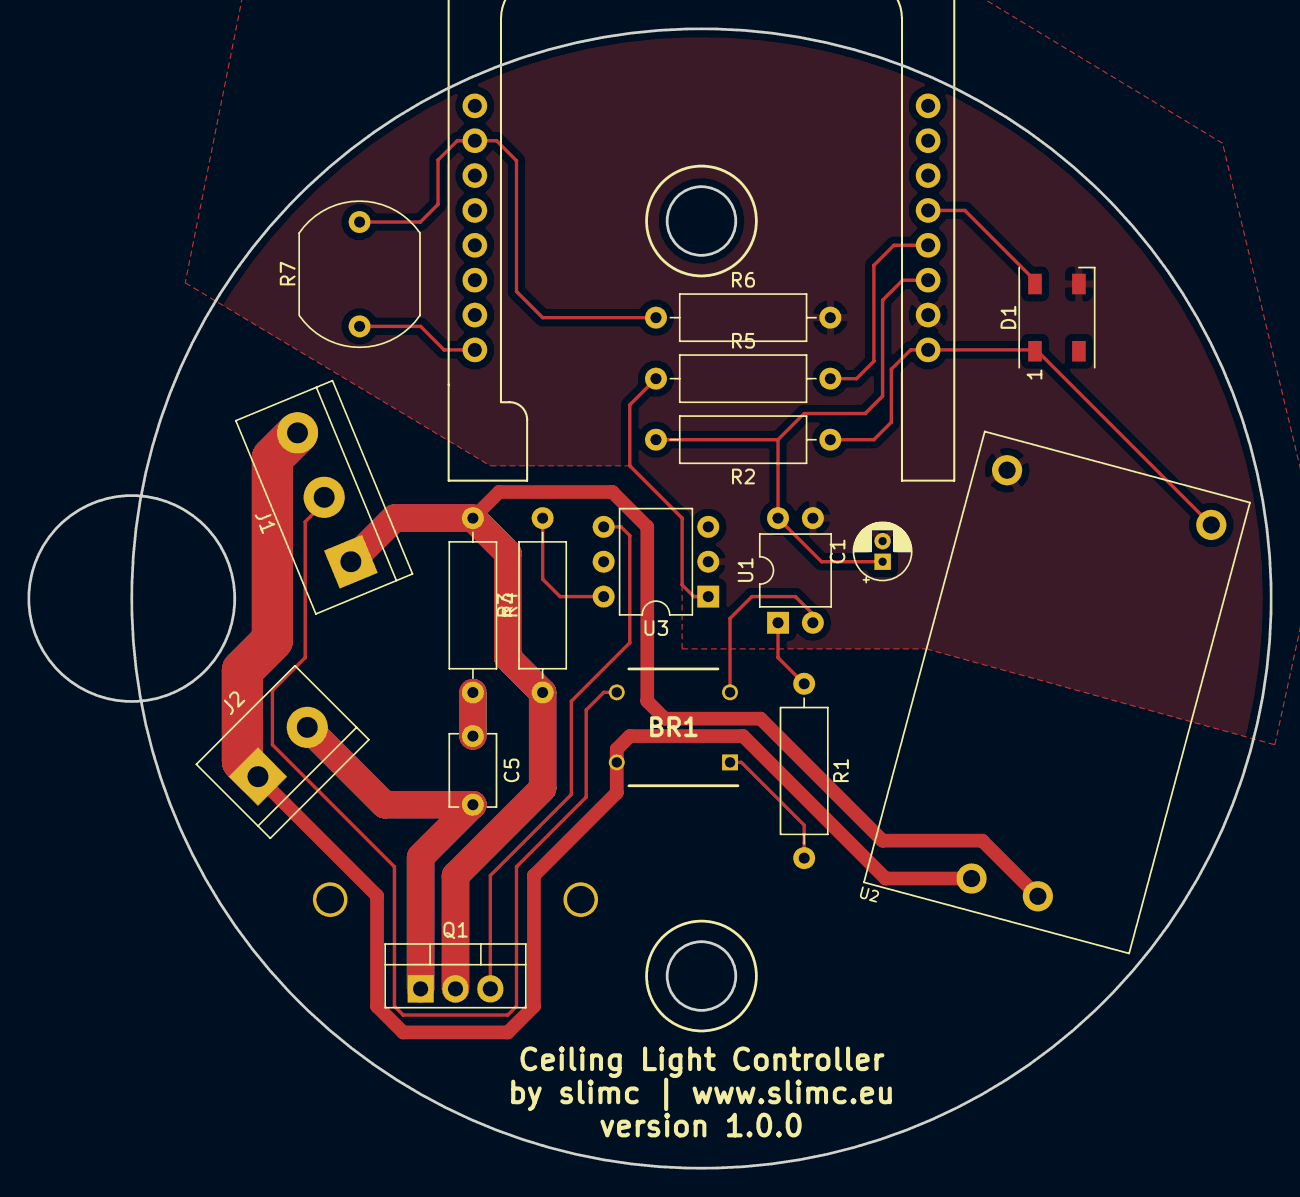
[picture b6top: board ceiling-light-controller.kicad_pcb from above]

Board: 2 copper layers, 90.5 x 83.0 mm, 18 parts (0 on the bottom side), 18 nets.

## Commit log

2019-05-09 basic schematic for ceiling light controller to be tested
2019-05-09 small changes
2019-05-25 renaming
2019-05-25 library submodule
2019-05-25 new AD-DC conv; footprint refs; simple PCB
2019-05-26 LED, LDR; PCB layout; copper traces
2019-05-26 gerber files and order sample
2019-05-27 changed absolute paths to
2019-05-27 moved submodules
2019-05-27 added readme
2019-05-27 empty Arduino file
2019-05-27 fixing submodule path once again
2019-05-27 submodule fixed; hardware directory
2019-05-27 ceiling light readme update
2019-05-28 update to PCB layput
2019-05-29 name change and symbolic path for libs
2019-05-29 symbol library removed
2019-05-29 readme update
2019-06-07 improved schematic layout view; missing new PCB layout
2019-06-07 PlatformIO setup testing
2019-06-07 readme updates
2019-06-07 markdown test
2019-06-07 more readme tests
2019-06-07 circuit images exports
2019-06-07 Schematic changes; PCB component placement, no traces
2019-06-07 TO220 Triode Heatsink update
2019-06-12 HTML PCB viewer
2019-06-14 new PCB layout and traces for mains light controller
2019-06-17 platformio OTA test
2019-06-17 gerbers export
2019-06-17 PlatformIO OTA working
2019-06-18 WiFi, StatusLED and MQTT tests
2019-06-25 MQTT duty reporting
2019-06-26 output control via MQTT and switch working
2019-06-26 clean up
2019-06-28 WiFiManager for MQTT server
2019-06-28 fresh export of drawings
2019-07-01 non-blocking reconnect for mqtt and wifi
2019-07-01 work on device info
2019-07-01 removed wifimanager device location option and refined mqtt topics
2019-07-21 pcb updates
2019-07-22 load switching with FL5150
2019-07-25 mlc dimmerable edition in own directory
2019-07-26 Directory for development of radiator valve
2019-07-27 renaming mains-light-controller to ceiling-light
2019-07-27 remove old mains light controller directories
2019-07-27 vscode workspace
2019-07-27 small repo cleanup
2019-07-27 mailbox sensor directory
2019-08-02 work on dimmable circuit and git submodules
2019-08-02 git submodule fixing
2019-08-02 fixed submodule
2019-08-02 submodule update and plot export
2019-08-02 kicad lib/fp path fix
2019-08-02 symbol was misaligned
2019-08-03 work on dimmable schematic
2019-08-03 fixed deps issue
2019-08-06 PCB layout for v1.1.0 through hole prototype
2019-08-06 removed old undimmable version
2019-08-06 began on 3d models
2019-08-11 new schematic layout
2019-08-16 work on dimmable ceiling light
2019-08-17 RGBW controller pt test code
2019-08-19 added library for ESP FTDI programming adapter
2019-08-19 changed schematic layout
2019-08-19 structured configuration code
2019-08-19 improving schematic
2019-08-19 adjusted schematic
2019-08-19 schematic update
2019-08-20 work on schematic
2019-08-23 moving away from FL5150
2019-08-23 schematic work
2019-08-23 RGBW firmware experimenting
2019-09-03 mailbox-sensor work
2019-09-16 ws2812b strip
2019-09-16 moved files; 3v3 to 5v logic
2019-10-07 FL51xx breadboard adapter
2019-10-07 new design
2019-10-07 removed duplicates
2019-10-07 first order
2019-10-08 adjusted component values

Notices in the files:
ceiling-light-controller/hardware/ceiling-light-controller.sch:
creativecommons.org/licenses/by/4.0
License: CC BY 4.0
